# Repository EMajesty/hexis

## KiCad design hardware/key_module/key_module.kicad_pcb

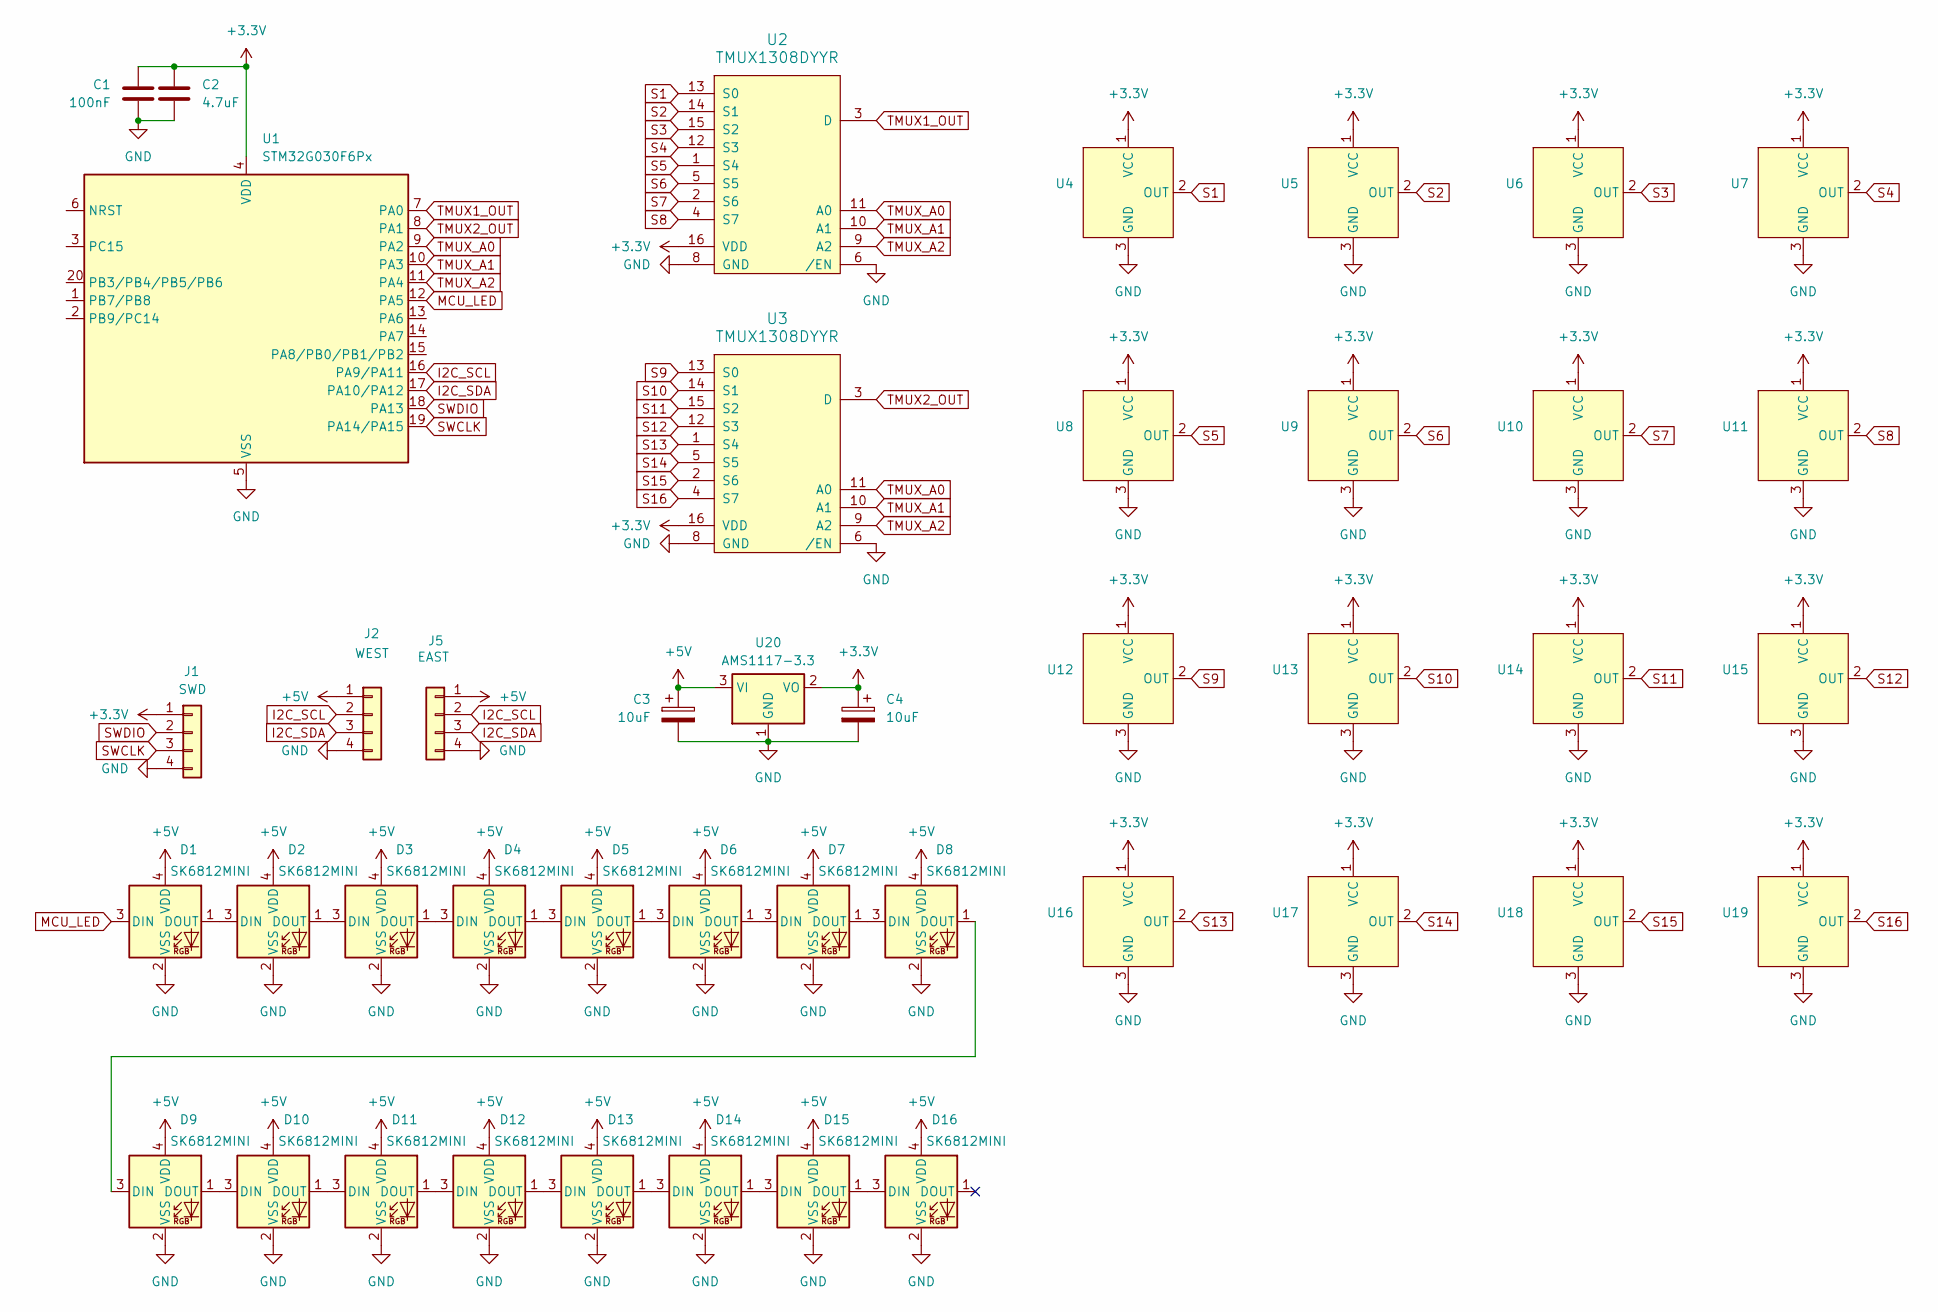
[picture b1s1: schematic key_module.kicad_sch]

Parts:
C1: 100nF; CP_EIA-2012-12_Kemet-R_HandSolder
C2: 4.7uF; CP_EIA-2012-12_Kemet-R_HandSolder
C3, C4: 10uF; CP_EIA-2012-12_Kemet-R_HandSolder
D1, D2, D3, D4, D5, D6, D7, D8, D9, D10, D11, D12, D13, D14, D15, D16: SK6812MINI; LED_SK6812MINI_PLCC4_3.5x3.5mm_P1.75mm
J1: SWD; PinHeader_1x04_P2.54mm_Vertical
J2: WEST; PinHeader_1x06_P2.54mm_Horizontal
J5: EAST; PinSocket_1x06_P2.54mm_Horizontal
U1: STM32G030F6Px; TSSOP-20_4.4x6.5mm_P0.65mm
U2, U3: TMUX1308DYYR; SOT-23-THIN-16; Part Number TMUX1308DYYR; JLCPCB ID C2877584
U4, U5, U6, U7, U8, U9, U10, U11, U12, U13, U14, U15, U16, U17, U18, U19: HE
U20: AMS1117-3.3; SOT-223-3_TabPin2

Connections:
+3.3V: C1.1, C2.1, C4.1, J1.1, U1.4 (VDD), U2.16 (VDD), U3.16 (VDD), U4.1 (VCC), U5.1 (VCC), U6.1 (VCC), U7.1 (VCC), U8.1 (VCC), U9.1 (VCC), U10.1 (VCC), U11.1 (VCC), U12.1 (VCC), U13.1 (VCC), U14.1 (VCC), U15.1 (VCC), U16.1 (VCC), U17.1 (VCC), U18.1 (VCC), U19.1 (VCC), U20.2 (VO)
+5V: C3.1, D1.4 (VDD), D2.4 (VDD), D3.4 (VDD), D4.4 (VDD), D5.4 (VDD), D6.4 (VDD), D7.4 (VDD), D8.4 (VDD), D9.4 (VDD), D10.4 (VDD), D11.4 (VDD), D12.4 (VDD), D13.4 (VDD), D14.4 (VDD), D15.4 (VDD), D16.4 (VDD), J2.1, J5.1, U20.3 (VI)
GND: C1.2, C2.2, C3.2, C4.2, D1.2 (VSS), D2.2 (VSS), D3.2 (VSS), D4.2 (VSS), D5.2 (VSS), D6.2 (VSS), D7.2 (VSS), D8.2 (VSS), D9.2 (VSS), D10.2 (VSS), D11.2 (VSS), D12.2 (VSS), D13.2 (VSS), D14.2 (VSS), D15.2 (VSS), D16.2 (VSS), J1.4, J2.4, J5.4, U1.5 (VSS), U2.6 (/EN), U2.8 (GND), U3.6 (/EN), U3.8 (GND), U4.3 (GND), U5.3 (GND), U6.3 (GND), U7.3 (GND), U8.3 (GND), U9.3 (GND), U10.3 (GND), U11.3 (GND), U12.3 (GND), U13.3 (GND), U14.3 (GND), U15.3 (GND), U16.3 (GND), U17.3 (GND), U18.3 (GND), U19.3 (GND), U20.1 (GND)
I2C_SCL: J2.2, J5.2, U1.16 (PA9/PA11)
I2C_SDA: J2.3, J5.3, U1.17 (PA10/PA12)
MCU_LED: D1.3 (DIN), U1.12 (PA5)
unnamed: D1.1 (DOUT), D2.3 (DIN)
unnamed: D2.1 (DOUT), D3.3 (DIN)
unnamed: D3.1 (DOUT), D4.3 (DIN)
unnamed: D4.1 (DOUT), D5.3 (DIN)
unnamed: D5.1 (DOUT), D6.3 (DIN)
unnamed: D6.1 (DOUT), D7.3 (DIN)
unnamed: D7.1 (DOUT), D8.3 (DIN)
unnamed: D8.1 (DOUT), D9.3 (DIN)
unnamed: D9.1 (DOUT), D10.3 (DIN)
unnamed: D10.1 (DOUT), D11.3 (DIN)
unnamed: D11.1 (DOUT), D12.3 (DIN)
unnamed: D12.1 (DOUT), D13.3 (DIN)
unnamed: D13.1 (DOUT), D14.3 (DIN)
unnamed: D14.1 (DOUT), D15.3 (DIN)
unnamed: D15.1 (DOUT), D16.3 (DIN)
S1: U2.13 (S0), U4.2 (OUT)
S2: U2.14 (S1), U5.2 (OUT)
S3: U2.15 (S2), U6.2 (OUT)
S4: U2.12 (S3), U7.2 (OUT)
S5: U2.1 (S4), U8.2 (OUT)
S6: U2.5 (S5), U9.2 (OUT)
S7: U2.2 (S6), U10.2 (OUT)
S8: U2.4 (S7), U11.2 (OUT)
S9: U3.13 (S0), U12.2 (OUT)
S10: U3.14 (S1), U13.2 (OUT)
S11: U3.15 (S2), U14.2 (OUT)
S12: U3.12 (S3), U15.2 (OUT)
S13: U3.1 (S4), U16.2 (OUT)
S14: U3.5 (S5), U17.2 (OUT)
S15: U3.2 (S6), U18.2 (OUT)
S16: U3.4 (S7), U19.2 (OUT)
SWCLK: J1.3, U1.19 (PA14/PA15)
SWDIO: J1.2, U1.18 (PA13)
TMUX1_OUT: U1.7 (PA0), U2.3 (D)
TMUX2_OUT: U1.8 (PA1), U3.3 (D)
TMUX_A0: U1.9 (PA2), U2.11 (A0), U3.11 (A0)
TMUX_A1: U1.10 (PA3), U2.10 (A1), U3.10 (A1)
TMUX_A2: U1.11 (PA4), U2.9 (A2), U3.9 (A2)

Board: 2 copper layers, 43 parts (10 on the bottom side), 44 nets, no tracks yet.

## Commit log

2026-06-12 Add gitignore rules for PlatformIO, clangd, and KiCad
2026-06-12 Replace firmware and hardware .gitignore files with .gitkeep placeholders
2026-06-12 Add initial KiCad brain and key_module board projects
2026-06-13 Remove brain board project and consolidate into key_module
